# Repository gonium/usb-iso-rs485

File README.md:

# An isolated USB-RS485 adapter

I connected a lot of USB-RS485 adapters to my [smart meter readout
software](https://github.com/gonium/gosdm630) and wasn't happy. Either
the device is cheap and broken or works but is very expensive. The
supercheap adaptors from China often provice no ground connection, one
worked fine, another one was unstable. Both did not adhere to the USB
spec (90mA initial current draw limit). On the other hand, industrial
adaptors like the Meilhaus RedCOM USB-COMi-SI or the ADAM 4561 isolate
the RS-485 bus from the USB line and work extremely reliable. But they
are really expensive.

This project aims to create an adaptor that works well and is reasonably
priced. We use the following components:

* An FTDI FT232L provides the USB-UART interface and can be configured
for RS485 operation.
* An [Analog Devices
ADM2582E](http://www.analog.com/media/en/technical-documentation/data-sheets/ADM2582E_2587E.pdf)
isolates the RS485 bus and generates the supply voltage for the bus.
Please note: this device is rather expensive, but Analog Devices will
send you samples at no cost.
* We use WAGO 233 series connectors to connect to the RS485 bus

The first prototype looks like this:

The PCB is too big, and I don't need all those test points any more.
Therefore, I have build the second prototype. Please note that the board
is slightly smaller, has a different WAGO connector and unpopulated
footprints for protection diodes:

The second prototype works quite well. Unfortunately, the holes for the
WAGO connector are too small -- I needed to drill them bigger. While
doing so, I destroyed a connection to the "A" pin - the copper wire to
the right of the WAGO connector replaces the PCB trace I destroyed. In
addition, the footprint for the MOSFET is wrong.

Minor layout changes are needed, but the principle is solid.

# TODO

* Copy all footprints to project library
* Footprint of MOSFET is wrong
* Increase hole diameter for WAGO connector
* Fix position of silkscreen on bottom layer

# FTDI configuration.

The FTDI chip needs to be configured in order to work in this
application. Specifically, the following changes need to be written into
its EEPROM:

* CBUS3 must be set to PwrEN. This ensures that the device draws only 90
mA when plugged in. After completing the USB enumeration process, this
pin triggers the onboard MOSFET and the remainder of the board is
powered up.
* CBUS4 must be set to TxDEN. The FTDI toggles the nRE pin of the ADM2582.

You can use [Mark Lord's ft232r_prog](http://rtr.ca/ft232r/) to change
the EEPROM settings. In order to see the current EEPROM content, use

    $ ft232r_prog --verbose --dump --old-vid 0x0403 --old-pid 0x6001

In order to set CBUS3 to PwrEN, CBUS4 to TxDEN, high-current-io off and
the maximum power consumption to 300 mA, use

    $ ft232r_prog --verbose --dump --old-vid 0x0403 --old-pid 0x6001 \
		--cbus3 PwrEn --cbus4 TxDEN --high-current-io off --max-bus-power 300

On Linux I could successfully compile the binary just by typing
``make`` and using it as described above. On Mac OS X, I needed to add
``/usr/local`` to the Makefile. The top two lines now read like this:

    CFLAGS = -Wall -O2 -s -Werror -I/usr/local/include
    LDFLAGS = -L/usr/local/lib -lusb -lftdi -s

In my case, a FTDI driver claimed the device, preventing the
``ft232r_prog`` command to communicate with the FTDI. You can list the
FTDI-related kernel extensions using

    $ kextstat | grep FTDI
		156    0 0xffffff7f83606000 0x8000     0x8000     com.FTDI.driver.FTDIUSBSerialDriver (2.2.16) 0AB01558-B114-9EF2-1CD9-A13CFA557737 <137 55 5 4 3 1>

Then, to unload the driver, use

    $ sudo kextunload -b com.FTDI.driver.FTDIUSBSerialDriver

for all FTDI drivers you found.

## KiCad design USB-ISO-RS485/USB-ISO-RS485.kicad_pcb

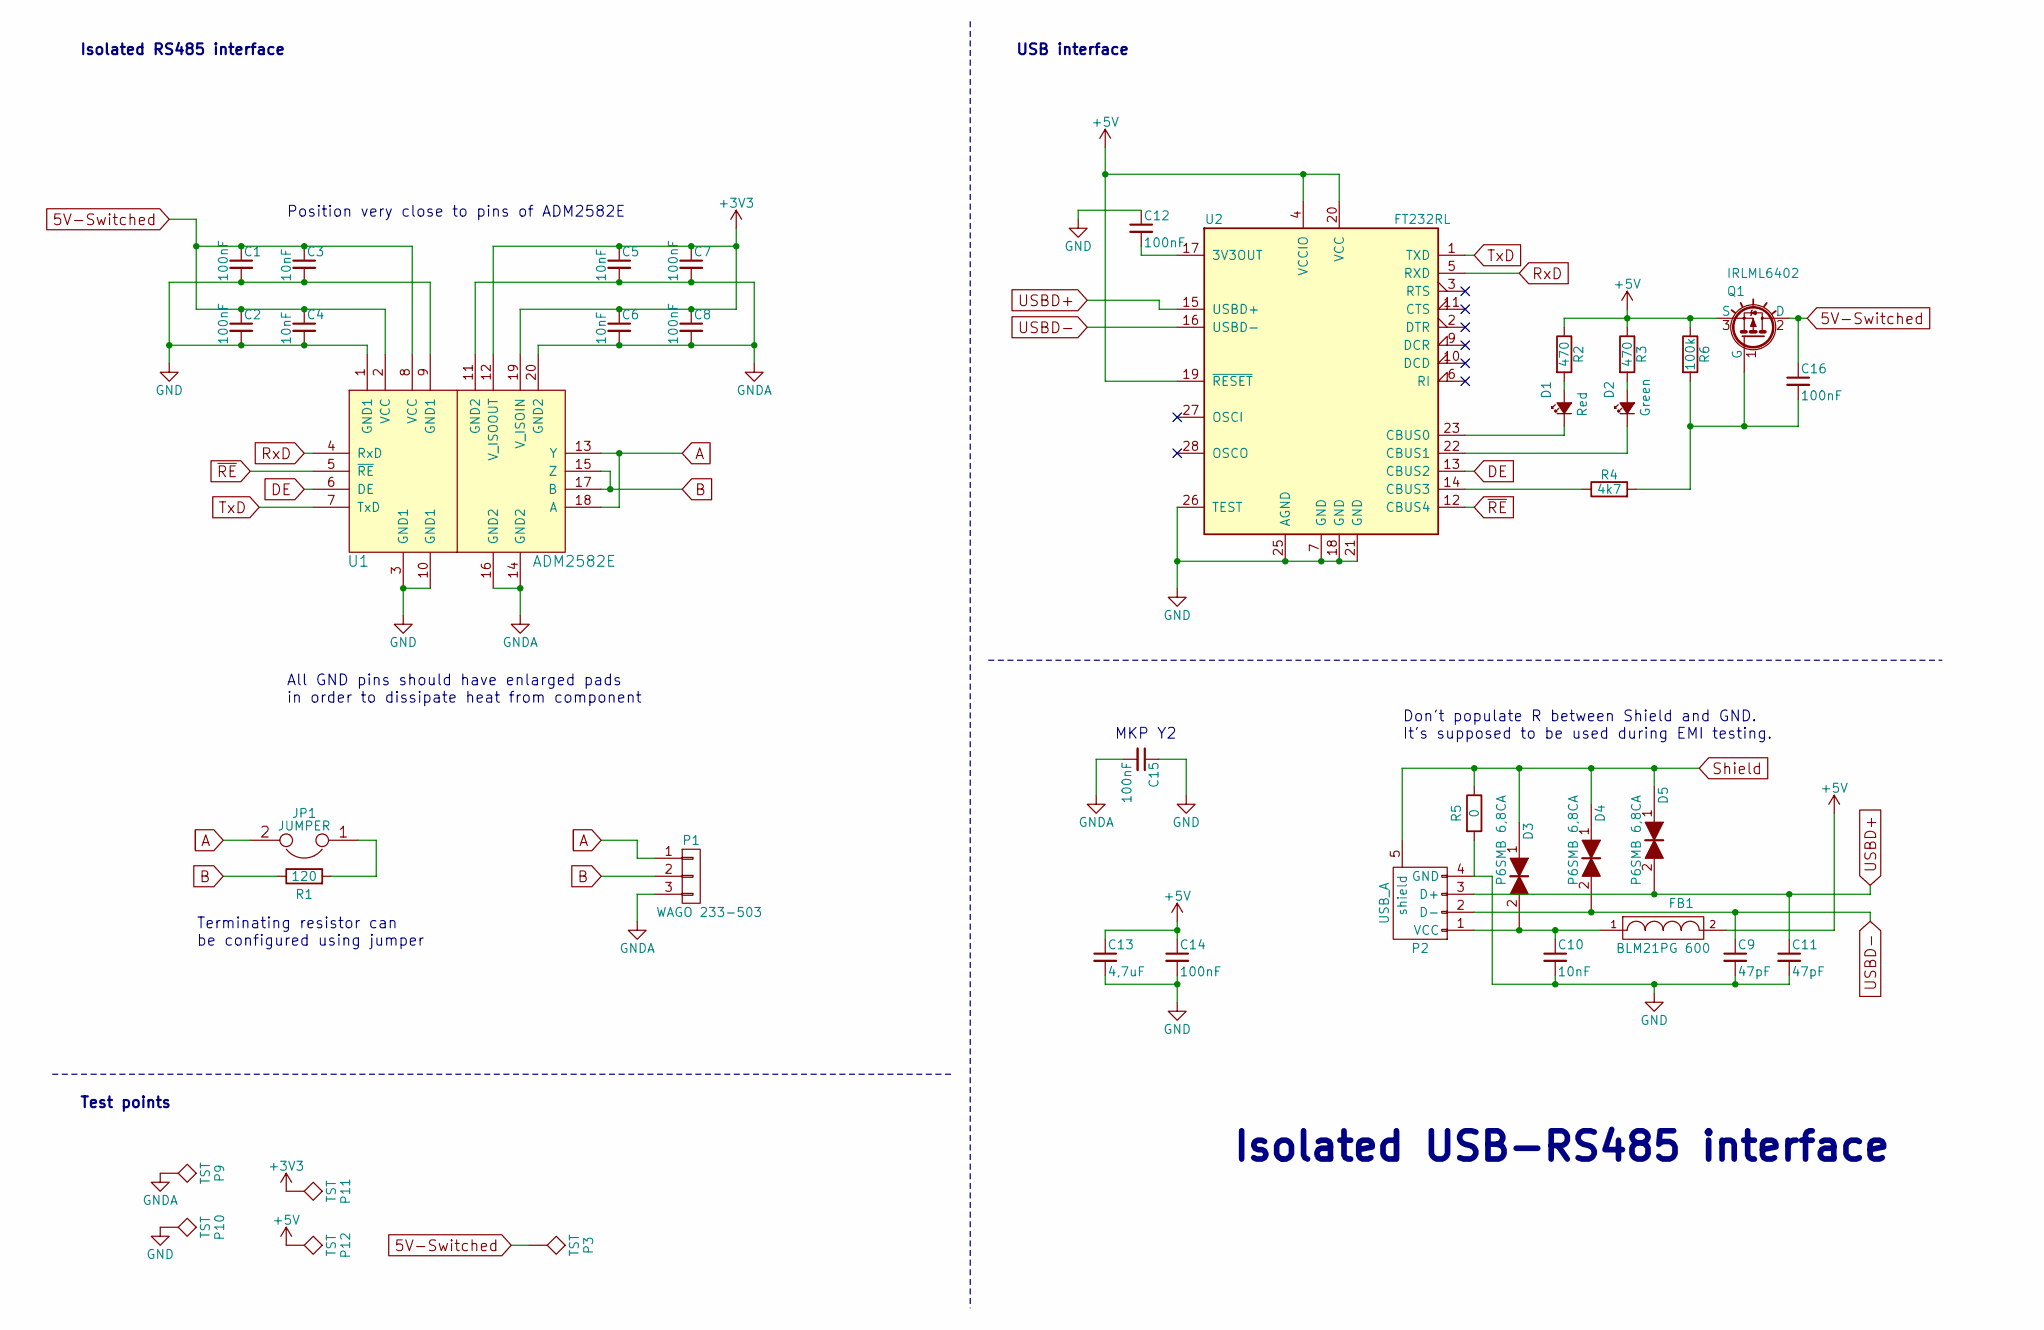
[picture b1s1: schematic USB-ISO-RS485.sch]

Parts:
C1, C2, C7, C8, C12, C14, C16: 100nF; C_0805_HandSoldering
C3, C4, C5, C6, C10: 10nF; C_0805_HandSoldering
C9, C11: 47pF; C_0805_HandSoldering
C13: 4,7uF; C_0805_HandSoldering
C15: 100nF; C_Rect_L26.5mm_W7.0mm_P22.50mm_MKS4
D1: Red; LED_0805
D2: Green; LED_0805
D3, D4, D5: P6SMB 6,8CA; P6SMB6,8CA
FB1: BLM21PG 600; R_0805_HandSoldering
JP1: JUMPER; Pin_Header_Straight_1x02_Pitch2.54mm
P1: WAGO 233-503; WAGO233-503
P2: USB_A; USB_B
P3, P9, P10, P11, P12: TST; Measurement_Point_Round-TH_Small
Q1: IRLML6402
R1: 120; R_0805_HandSoldering
R2, R3: 470; R_0805_HandSoldering
R4: 4k7; R_0805_HandSoldering
R5: 0; R_0805_HandSoldering
R6: 100k; R_0805_HandSoldering
U1: ADM2582E; ADM2582E-SOIC20W-Thermal-Correct
U2: FT232RL; SSOP-28_5.3x10.2mm_Pitch0.65mm

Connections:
5V-Switched: C1.1, C2.1, C3.1, C4.1, C16.1, P3.1, Q1.2 (D), U1.2 (VCC), U1.8 (VCC)
+3V3: C5.1, C6.1, C7.1, C8.1, P11.1, U1.12 (V_ISOOUT), U1.19 (V_ISOIN)
+5V: C13.1, C14.1, FB1.2, P12.1, Q1.3 (S), R2.1, R3.1, R6.1, U2.4 (VCCIO), U2.19 (~RESET~), U2.20 (VCC)
A: JP1.2, P1.1, U1.13 (Y), U1.18 (A)
B: P1.2, R1.1, U1.15 (Z), U1.17 (B)
DE: U1.6 (DE), U2.13 (CBUS2)
GND: C1.2, C2.2, C3.2, C4.2, C9.2, C10.2, C11.2, C12.1, C13.2, C14.2, C15.1, P2.4 (GND), P10.1, R5.2, U1.1 (GND1), U1.3 (GND1), U1.9 (GND1), U1.10 (GND1), U2.7 (GND), U2.18 (GND), U2.21 (GND), U2.25 (AGND), U2.26 (TEST)
GNDA: C5.2, C6.2, C7.2, C8.2, C15.2, P1.3, P9.1, U1.11 (GND2), U1.14 (GND2), U1.16 (GND2), U1.20 (GND2)
unnamed: C10.1, D3.2, FB1.1, P2.1 (VCC)
unnamed: C12.2, U2.17 (3V3OUT)
unnamed: C16.2, Q1.1 (G), R4.2, R6.2
unnamed: D1.1 (K), U2.23 (CBUS0)
unnamed: D1.2 (A), R2.2
unnamed: D2.1 (K), U2.22 (CBUS1)
unnamed: D2.2 (A), R3.2
unnamed: JP1.1, R1.2
unnamed: R4.1, U2.14 (CBUS3)
RxD: U1.4 (RxD), U2.5 (RXD)
Shield: D3.1, D4.1, D5.1, P2.5 (shield), R5.1
TxD: U1.7 (TxD), U2.1 (TXD)
USBD+: C11.1, D5.2, P2.3 (D+), U2.15 (USBD+)
USBD-: C9.1, D4.2, P2.2 (D-), U2.16 (USBD-)
~RE: U1.5 (~RE), U2.12 (CBUS4)

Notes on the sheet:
Position very close to pins of ADM2582E
All GND pins should have enlarged pads in order to dissipate heat from component
Terminating resistor can be configured using jumper
USB interface
Isolated RS485 interface
Isolated USB-RS485 interface
Test points
MKP Y2
Don't populate R between Shield and GND. It's supposed to be used during EMI testing.

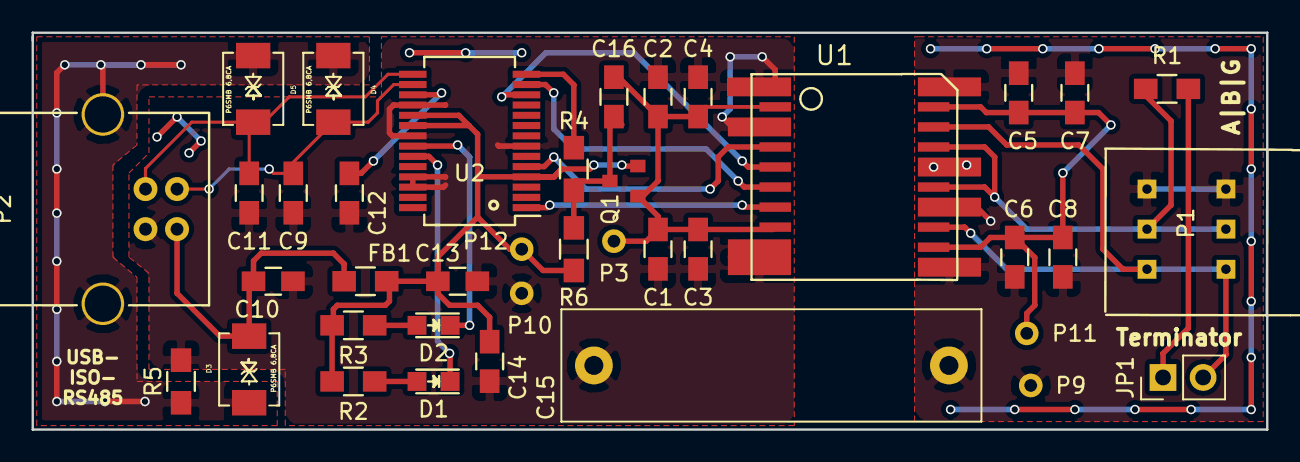
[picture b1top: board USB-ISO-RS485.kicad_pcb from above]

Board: 2 copper layers, 78.2 x 25.1 mm, 39 parts (0 on the bottom side), 23 nets.

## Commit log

2017-05-07 schematic completed
2017-05-07 Added UART interface header, exported schematic as PDF
2017-05-07 layout
2017-05-13 assigned all footprints
2017-05-14 broken layout - ADM2582E footprint to narrow
2017-05-14 added corrected footprint, rerouted board
2017-05-27 started first build
2017-05-29 txden
2017-05-30 completed TODO list, added commandline example for setting the FTDI bus power report
2017-06-01 added frequency response estimation script
2017-06-18 added switching USB power, shielding separated, added TVS & EMI filter on USB line
2017-06-18 added note regarding PWREN config
2017-06-18 new PDF export
2017-06-20 created new footprints & completed association.
2017-06-25 v0.2 board layout complete
2017-06-30 added platformio example code
2017-07-09 working on v0.2
2017-07-19 experimenting
2017-07-19 updated todo list
2017-08-04 cleanup
2017-08-04 proper documentation and photos
2017-08-04 image description, order note

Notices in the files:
USB-ISO-RS485/USB-ISO-RS485.kicad_pcb:
CC-BY-NC-SA
